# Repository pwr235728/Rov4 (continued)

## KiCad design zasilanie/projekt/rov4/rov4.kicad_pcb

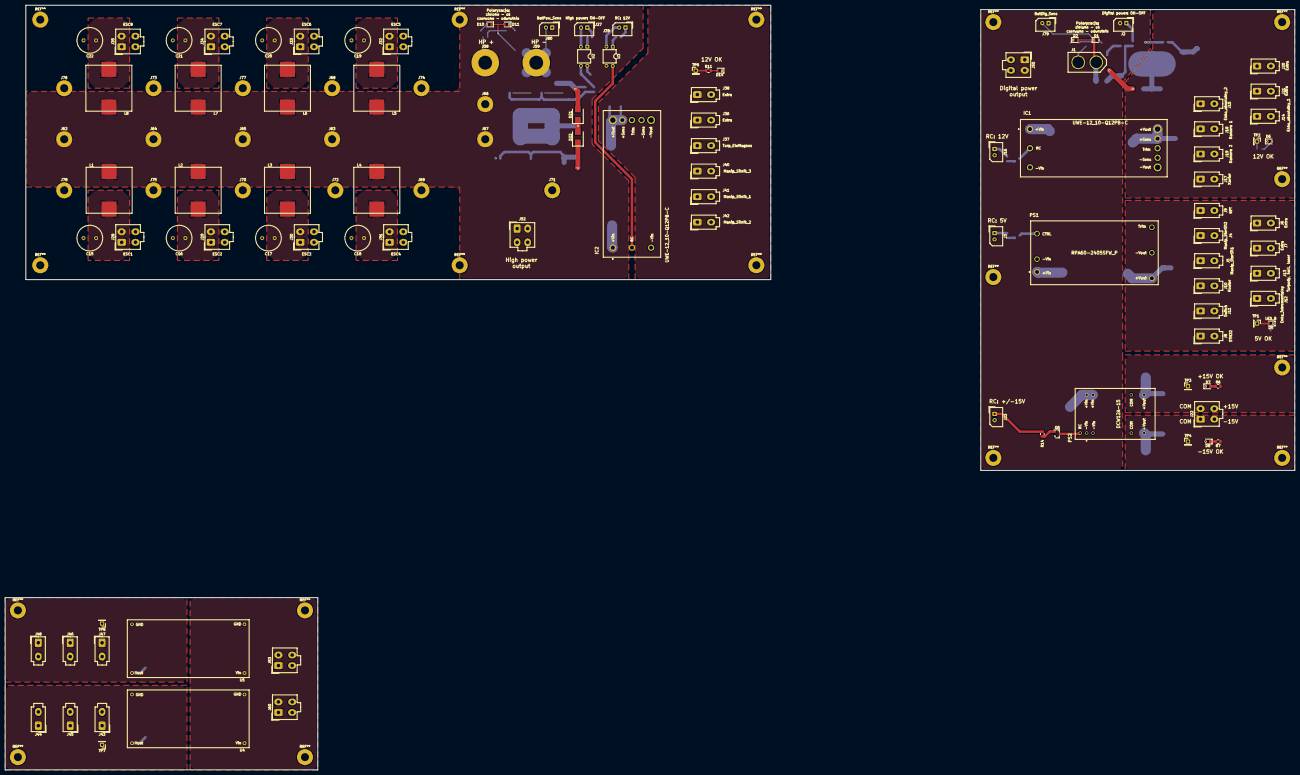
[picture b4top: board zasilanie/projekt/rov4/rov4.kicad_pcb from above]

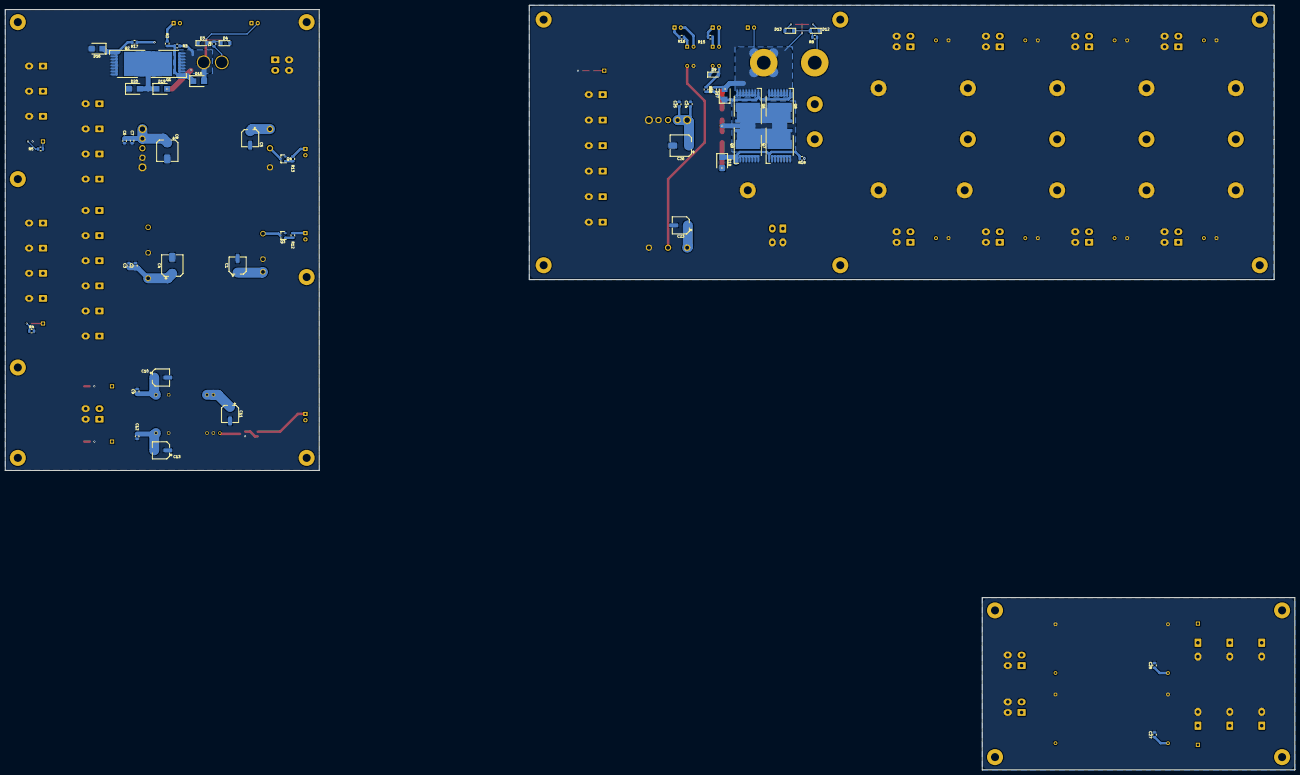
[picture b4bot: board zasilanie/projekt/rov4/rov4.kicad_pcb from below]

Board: 2 copper layers, 513.5 x 304.4 mm, 169 parts (52 on the bottom side), 58 nets.

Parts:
C1, C5, C11, C23: 33uF; CP_Elec_6.3x5.4
C2, C6, C9, C12, C24, C27, C28: 100nF; C_0805_2012Metric
C3, C7, C25: 10uF; C_0805_2012Metric
C4, C8, C26: 200uF; CP_Elec_8x10
C10, C13: 100uF; CP_Elec_6.3x7.7
C15, C16, C17, C18, C19, C20, C21, C22: C; C_Radial_D10.0mm_H20.0mm_P5.00mm
D1, D10: LED_G; LED_0805_2012Metric
D2, D11: LED_R; LED_0805_2012Metric
D3, D4, D9, D12, D13: BAT48; D_MiniMELF
D5, D6, D7, D8, D14: LED_B; LED_0805_2012Metric
D15, D16, D17, D18, D19, D20, D21, D22: D_TVS; D_SMB
IC1, IC2: UWE-12_10-Q12PB-C; UWE-12_10-Q12P-C
J1: Battery digital; XT60UPB-M
J2: Digital power: ON-OFF; Molex_SPOX_5267-02A_1x02_P2.50mm_Vertical
J3: RC_D_5V; Molex_SPOX_5267-02A_1x02_P2.50mm_Vertical
J4: Manip_SterSil2; Molex_Mini-Fit_Jr_5566-02A_2x01_P4.20mm_Vertical
J5: Manip_SterSil1; Molex_Mini-Fit_Jr_5566-02A_2x01_P4.20mm_Vertical
J6, J7, J20, J21, J36, J38, J44, J45, J47, J48: Extra; Molex_Mini-Fit_Jr_5566-02A_2x01_P4.20mm_Vertical
J8: STM32; Molex_Mini-Fit_Jr_5566-02A_2x01_P4.20mm_Vertical
J9: RPi; Molex_Mini-Fit_Jr_5566-02A_2x01_P4.20mm_Vertical
J10: Router; Molex_Mini-Fit_Jr_5566-02A_2x01_P4.20mm_Vertical
J11: Switch; Molex_Mini-Fit_Jr_5566-02A_2x01_P4.20mm_Vertical
J12: Enko_inkrementalny; Molex_Mini-Fit_Jr_5566-02A_2x01_P4.20mm_Vertical
J13: Torpedy, hall, laser; Molex_Mini-Fit_Jr_5566-02A_2x01_P4.20mm_Vertical
J14: Enko_absolutny_1; Molex_Mini-Fit_Jr_5566-02A_2x01_P4.20mm_Vertical
J15: Enko_absolutny_2; Molex_Mini-Fit_Jr_5566-02A_2x01_P4.20mm_Vertical
J16: RC_D_12V; Molex_SPOX_5267-02A_1x02_P2.50mm_Vertical
J17: Xavier; Molex_Mini-Fit_Jr_5566-02A_2x01_P4.20mm_Vertical
J18: Kamera 1; Molex_Mini-Fit_Jr_5566-02A_2x01_P4.20mm_Vertical
J19: Kamera 2; Molex_Mini-Fit_Jr_5566-02A_2x01_P4.20mm_Vertical
J22: hydrofony; Molex_Mini-Fit_Jr_5566-04A_2x02_P4.20mm_Vertical
J23: RC_D_15V; Molex_SPOX_5267-02A_1x02_P2.50mm_Vertical
J27: High power: ON-OFF; Molex_SPOX_5267-02A_1x02_P2.50mm_Vertical
J28: ESC1; Molex_Mini-Fit_Jr_5566-04A_2x02_P4.20mm_Vertical
J29: ESC2; Molex_Mini-Fit_Jr_5566-04A_2x02_P4.20mm_Vertical
J30: ESC3; Molex_Mini-Fit_Jr_5566-04A_2x02_P4.20mm_Vertical
J31: ESC4; Molex_Mini-Fit_Jr_5566-04A_2x02_P4.20mm_Vertical
J32: ESC5; Molex_Mini-Fit_Jr_5566-04A_2x02_P4.20mm_Vertical
J33: ESC6; Molex_Mini-Fit_Jr_5566-04A_2x02_P4.20mm_Vertical
J34: ESC7; Molex_Mini-Fit_Jr_5566-04A_2x02_P4.20mm_Vertical
J35: ESC8; Molex_Mini-Fit_Jr_5566-04A_2x02_P4.20mm_Vertical
J37: Torp_EleMagnes; Molex_Mini-Fit_Jr_5566-02A_2x01_P4.20mm_Vertical
J39: RC: 12V; Molex_SPOX_5267-02A_1x02_P2.50mm_Vertical
J40: Manip_Silnik_3; Molex_Mini-Fit_Jr_5566-02A_2x01_P4.20mm_Vertical
J41: Manip_Silnik_1; Molex_Mini-Fit_Jr_5566-02A_2x01_P4.20mm_Vertical
J42: Manip_Silnik_2; Molex_Mini-Fit_Jr_5566-02A_2x01_P4.20mm_Vertical
J43: Torpedy_serwo_7v; Molex_Mini-Fit_Jr_5566-02A_2x01_P4.20mm_Vertical
J46: Manip_serwo; Molex_Mini-Fit_Jr_5566-02A_2x01_P4.20mm_Vertical
J52, J60: HP_OUT; Molex_Mini-Fit_Jr_5566-04A_2x02_P4.20mm_Vertical
J53: HP_IN; Molex_Mini-Fit_Jr_5566-04A_2x02_P4.20mm_Vertical
J55: LP_OUT; Molex_Mini-Fit_Jr_5566-04A_2x02_P4.20mm_Vertical
J58: +BattPower; MountingHole_5.5mm_Pad
J59: -BattPower; MountingHole_5.5mm_Pad
J62, J63, J64, J65, J66, J67: bus_bar; MountingHole_3.2mm_M3_Pad
J68, J69, J70, J71, J72, J73, J74, J75, J76, J77, J78: bus_bar_bott; MountingHole_3.2mm_M3_Pad
J79: BatDig_Sens; Molex_SPOX_5267-02A_1x02_P2.50mm_Vertical
J80: BatPow_Sens; Molex_SPOX_5267-02A_1x02_P2.50mm_Vertical
L1, L2, L3, L4, L5, L6, L7, L8: L; 74435571100
PS1: RPA60-2405SFW_P
PS2: DCW12A-15
Q1, Q2, Q6, Q7, Q8, Q9: IPT004N03L; Infineon_PG-HSOF-8-1
Q3, Q4, Q5: BC847A; SOT-23
R1, R8: 3k; R_0805_2012Metric
R2, R9, R17, R18: 100; R_0805_2012Metric
R3, R10: 10k; R_0805_2012Metric
R4: 400; R_0805_2012Metric
R5, R11: 1k8; R_0805_2012Metric
R6, R7: 2k4; R_0805_2012Metric
R12, R13, R14: 3k3; R_0805_2012Metric
R15, R16: 680; R_0805_2012Metric
TP1, TP3: D_5V; PinHeader_1x01_P2.54mm_Vertical
TP2: D_12V; PinHeader_1x01_P2.54mm_Vertical
TP4: D_-5V; PinHeader_1x01_P2.54mm_Vertical
TP6: HP_12V; PinHeader_1x01_P2.54mm_Vertical
TP7: HP_7V; PinHeader_1x01_P2.54mm_Vertical
TP8: HP_5V; PinHeader_1x01_P2.54mm_Vertical
U2, U3: Transoptor; DIP-4_W7.62mm
U4, U5: lm2596; lm2596-44_8mm_x_23mm

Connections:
+BattDigit: C1.1, C5.1, C11.1, IC1.1, J1.1, J2.2, J55.1, J55.2, J79.1, PS1.1, PS2.22, PS2.23, R1.1, R17.1
+BattPow: C23.1, D9.1, IC2.1, J52.1, J52.2, J58.1, J62.1, J63.1, J64.1, J65.1, J66.1, J67.1, J80.1, L1.1, L2.1, L3.1, L4.1, L5.1, L6.1, L7.1, L8.1, R8.1, R18.1, U2.4
-BattDigit: C1.2, C2.2, C3.2, C4.2, C5.2, C6.2, C7.2, C8.2, C9.2, C10.2, C11.2, C12.1, C13.1, D6.1, D7.1, D8.2, D16.2, D20.1, IC1.3, IC1.4, IC1.5, J4.2, J5.2, J6.2, J7.2, J8.2, J9.2, J10.2, J11.2, J12.2, J13.2, J14.2, J15.2, J17.2, J18.2, J19.2, J20.2, J21.2, J22.3, J22.4, J55.3, J55.4, PS1.2, PS1.5, PS2.2, PS2.3, PS2.9, PS2.16, Q2.2, Q3.2, Q4.2, Q5.2, R4.2
-BattPow: C15.2, C16.2, C17.2, C18.2, C19.2, C20.2, C21.2, C22.2, C23.2, C24.2, C25.2, C26.2, D14.1, D18.2, D22.1, IC2.3, IC2.4, IC2.5, J28.3, J28.4, J29.3, J29.4, J30.3, J30.4, J31.3, J31.4, J32.3, J32.4, J33.3, J33.4, J34.3, J34.4, J35.3, J35.4, J36.2, J37.2, J38.2, J40.2, J41.2, J42.2, J52.3, J52.4, J68.1, J69.1, J70.1, J71.1, J72.1, J73.1, J74.1, J75.1, J76.1, J77.1, J78.1, Q7.2, Q9.2, U3.3
/logika_main/-Batt: D1.1, D2.2, D15.2, D19.2, J1.2, J79.2, Q1.2, R3.2
unnamed: C2.1, C3.1, C4.1, D5.2, J4.1, J5.1, J6.1, J7.1, J8.1, J9.1, J10.1, J11.1, J12.1, J13.1, PS1.6, TP1.1
unnamed: C6.1, C7.1, C8.1, IC1.7, IC1.8, J14.1, J15.1, J17.1, J18.1, J19.1, J20.1, J21.1, R5.2, TP2.1
unnamed: C9.1, C10.1, J22.2, PS2.14, R6.2, TP3.1
unnamed: C12.2, C13.2, J22.1, PS2.11, R7.1, TP4.1
unnamed: C15.1, J28.1, J28.2, L1.2
unnamed: C16.1, J29.1, J29.2, L2.2
unnamed: C17.1, J30.1, J30.2, L3.2
unnamed: C18.1, J31.1, J31.2, L4.2
unnamed: C19.1, J32.1, J32.2, L5.2
unnamed: C20.1, J33.1, J33.2, L6.2
unnamed: C21.1, J34.1, J34.2, L7.2
unnamed: C22.1, J35.1, J35.2, L8.2
unnamed: C24.1, C25.1, C26.1, IC2.7, IC2.8, J36.1, J37.1, J38.1, J40.1, J41.1, J42.1, R11.1, TP6.1
unnamed: C27.1, J43.1, J44.1, J45.1, TP7.1, U4.3
unnamed: C27.2, C28.2, J43.2, J44.2, J45.2, J46.2, J47.2, J48.2, J53.3, J53.4, J60.3, J60.4, U4.2, U4.4, U5.2, U5.4
unnamed: C28.1, J46.1, J47.1, J48.1, TP8.1, U5.3
unnamed: D1.2, D3.1
unnamed: D2.1, D4.2
unnamed: D3.2, D4.1, R1.2
unnamed: D5.1, R4.1
unnamed: D6.2, R5.1
unnamed: D7.2, R6.1
unnamed: D8.1, R7.2
unnamed: D9.2, R9.1, U2.3
unnamed: D10.1, D11.2, D17.2, D21.2, J59.1, J80.2, Q6.2, Q8.2, R10.2
unnamed: D10.2, D12.1
unnamed: D11.1, D13.2
unnamed: D12.2, D13.1, R8.2
unnamed: D14.2, R11.2
unnamed: D15.1, Q1.1, R2.2, R3.1
unnamed: D16.1, Q2.1, R17.2
unnamed: D17.1, Q6.1, Q8.1, R9.2, R10.1
unnamed: D18.1, Q7.1, Q9.1, R18.2
unnamed: D19.1, D20.2, Q1.3, Q2.3
unnamed: D21.1, D22.2, Q6.3, Q7.3, Q8.3, Q9.3
unnamed: IC1.2, Q4.3
unnamed: IC2.2, U3.4
unnamed: J2.1, R2.1
unnamed: J3.1, R12.2
unnamed: J16.1, R13.2
unnamed: J23.1, R14.2
unnamed: J27.1, R15.2
unnamed: J27.2, U2.2
unnamed: J39.1, R16.2
unnamed: J39.2, U3.2
unnamed: J53.1, J53.2, J60.1, J60.2, U4.1, U5.1
unnamed: PS1.3, Q3.3
unnamed: PS2.1, Q5.3
unnamed: Q3.1, R12.1
unnamed: Q4.1, R13.1
unnamed: Q5.1, R14.1
unnamed: R15.1, U2.1
unnamed: R16.1, U3.1

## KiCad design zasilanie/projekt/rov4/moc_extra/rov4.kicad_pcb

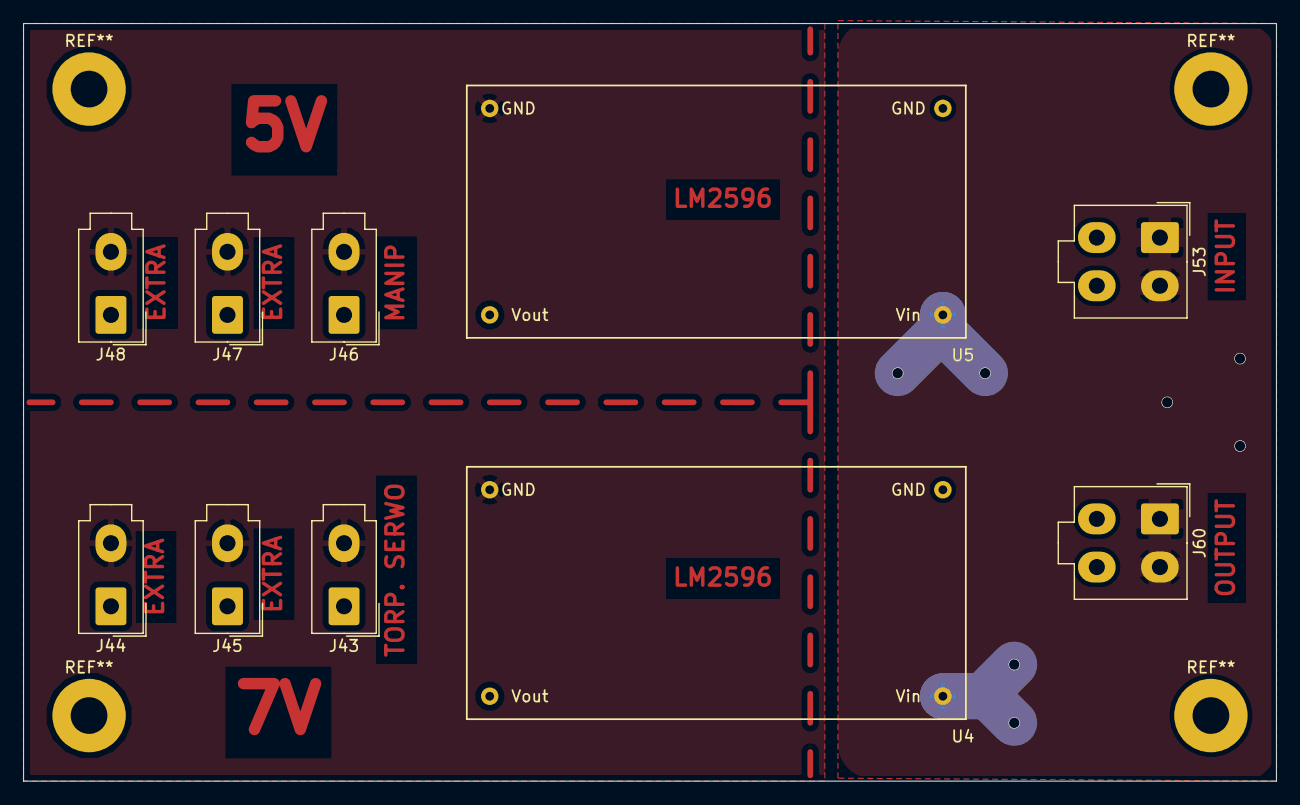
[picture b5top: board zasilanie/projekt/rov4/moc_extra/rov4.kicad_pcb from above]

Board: 2 copper layers, 109.2 x 66.0 mm, 10 parts (0 on the bottom side), 4 nets.

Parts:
J43: Torpedy_serwo_7v; Molex_Mini-Fit_Jr_5566-02A_2x01_P4.20mm_Vertical
J44, J45, J47, J48: Extra; Molex_Mini-Fit_Jr_5566-02A_2x01_P4.20mm_Vertical
J46: Manip_serwo; Molex_Mini-Fit_Jr_5566-02A_2x01_P4.20mm_Vertical
J53: HP_IN; Molex_Mini-Fit_Jr_5566-04A_2x02_P4.20mm_Vertical
J60: HP_OUT; Molex_Mini-Fit_Jr_5566-04A_2x02_P4.20mm_Vertical
U4, U5: lm2596; lm2596-44_8mm_x_23mm

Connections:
unnamed: J43.1, J44.1, J45.1, U4.3
unnamed: J43.2, J44.2, J45.2, J46.2, J47.2, J48.2, J53.3, J53.4, J60.3, J60.4, U4.2, U4.4, U5.2, U5.4
unnamed: J46.1, J47.1, J48.1, U5.3
unnamed: J53.1, J53.2, J60.1, J60.2, U4.1, U5.1

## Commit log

2019-03-28 Adding existing files
2019-03-28 Modyfikacje schematu i PCB
2019-04-16 idea slotow
2019-04-25 sync
2019-04-27 test
2019-04-27 test2
2019-04-27 Reorganizacja struktury projektu
2019-04-27 Numerowanie elementów
2019-04-27 footprint list
2019-04-28 net-list
2019-04-28 pcb_logiczna rozstawienie footprintow
2019-04-28 poprawki do extra_pcb od logiki
2019-04-28 PCB: logika_main
2019-04-28 Model xt-60 pcb female
2019-04-28 xt-60 pcb male
2019-04-28 model: molex 2x2 socket pcb
2019-04-28 testowy plik step
2019-04-28 molex 1x2 socket pcb
2019-04-28 C_Radial_D10.0mm_H20.0mm_P5.00mm
2019-04-28 spox_2pin_socket_pcb
2019-04-28 Moc - filtry - pcb
2019-04-29 Modele 3D: lm2596 i xl4015
2019-04-29 logika_main.stp
2019-04-29 moc_main.stp
2019-04-29 moc_extra.stp
2019-04-29 moc_extra.stp fix
2019-04-29 moc_extra.stp fix2: lm2596 3d model
2019-04-29 Jakieś zmainy wszystkiego
2019-05-06 prawie gotowe xdd
2019-05-07 Ostatnie poprawki xd
2019-05-07 sprzątanie
2019-05-07 kosmetyka
2019-05-07 nowy step
2019-05-08 Fix + bus bary projekt
2019-06-03 battery on/off
2019-06-16 poprawki/schematy
2019-06-30 robust version
2019-06-30 removing copy
2019-07-02 capacitor bybpas
2019-07-08 new schematic
2019-07-08 power traces
2019-07-08 bus bar outline
2019-07-08 final
2019-07-12 drc fix
2019-07-13 visual fix
2019-07-13 poprawka schematów
2021-03-03 Some work
